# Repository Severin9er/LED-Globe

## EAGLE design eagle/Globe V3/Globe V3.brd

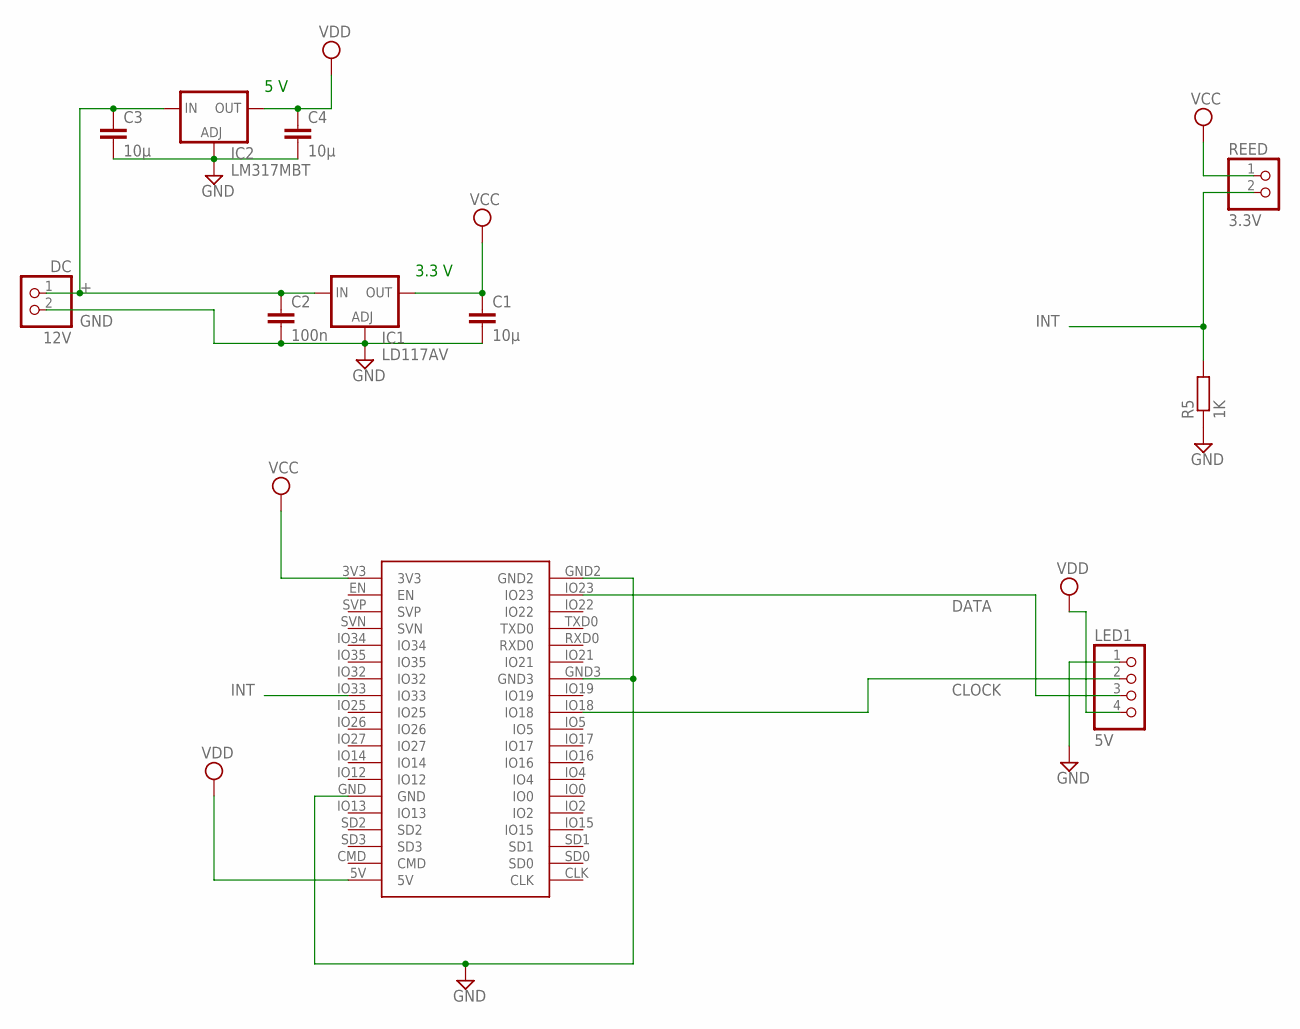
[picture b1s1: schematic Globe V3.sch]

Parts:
C1, C3, C4: 10µ; C025-024X044
C2: 100n; C050-024X044
DC: 12V; 1X02
IC1: LD117AV; TO220L1
IC2: LM317MBT; TO220L1
LED1: 5V; 1X04
R5: 1K; 0207/10
REED: 3.3V; 1X02
U$1: ESP32_DEVKITC

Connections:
+: C2.1, C3.1, DC.1, IC1.3 (IN), IC2.3 (IN)
CLOCK: LED1.2, U$1.IO18
DATA: LED1.3, U$1.IO23
GND: C1.2, C2.2, C3.2, C4.2, DC.2, IC1.1 (ADJ), IC2.1 (ADJ), LED1.1, R5.1, U$1.GND, U$1.GND2, U$1.GND3
INT: R5.2, REED.2, U$1.IO33
VCC: C1.1, IC1.2 (OUT), REED.1, U$1.3V3
VDD: C4.1, IC2.2 (OUT), LED1.4, U$1.5V

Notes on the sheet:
3.3 V
5 V

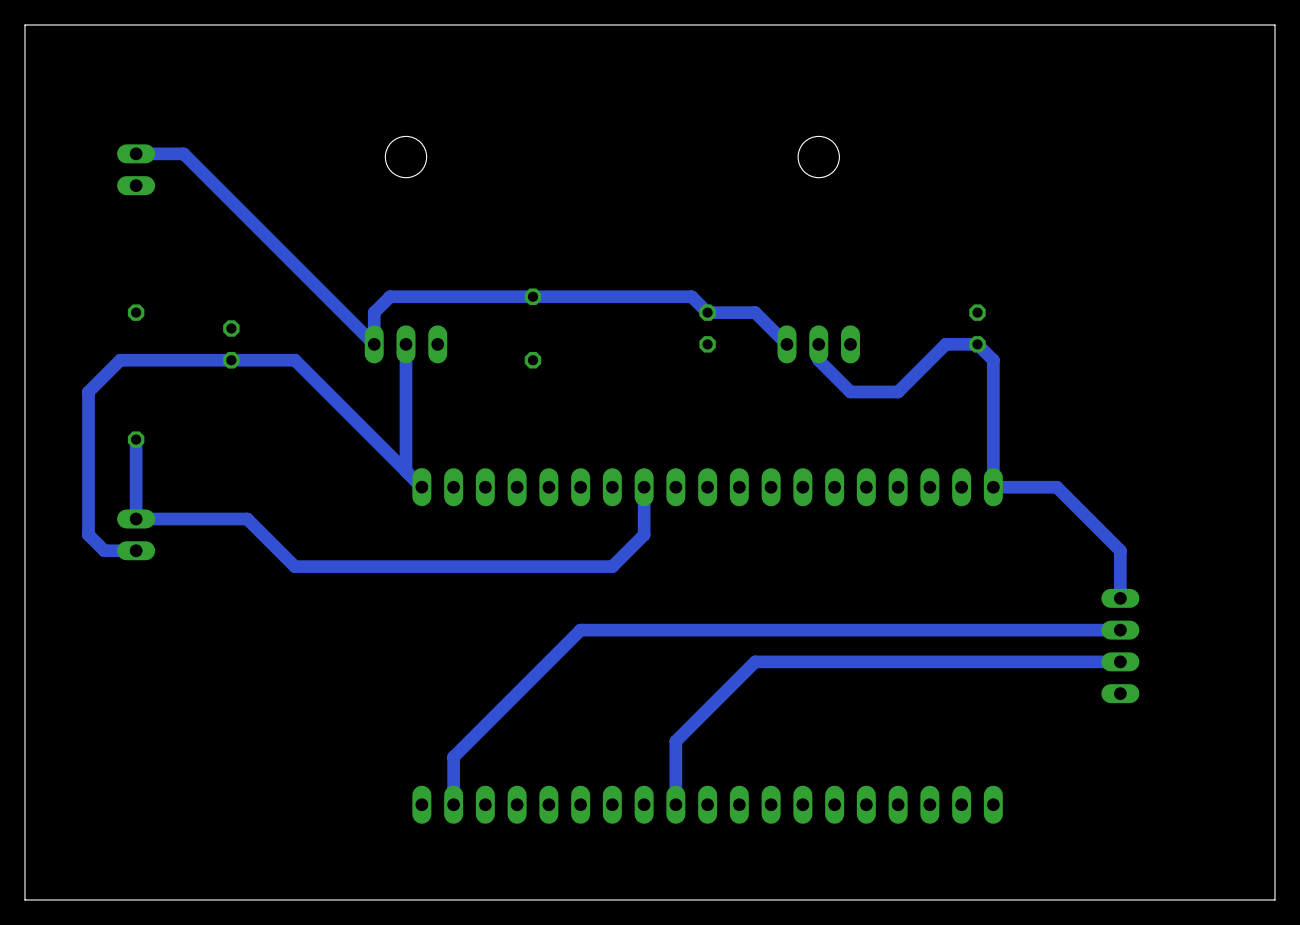
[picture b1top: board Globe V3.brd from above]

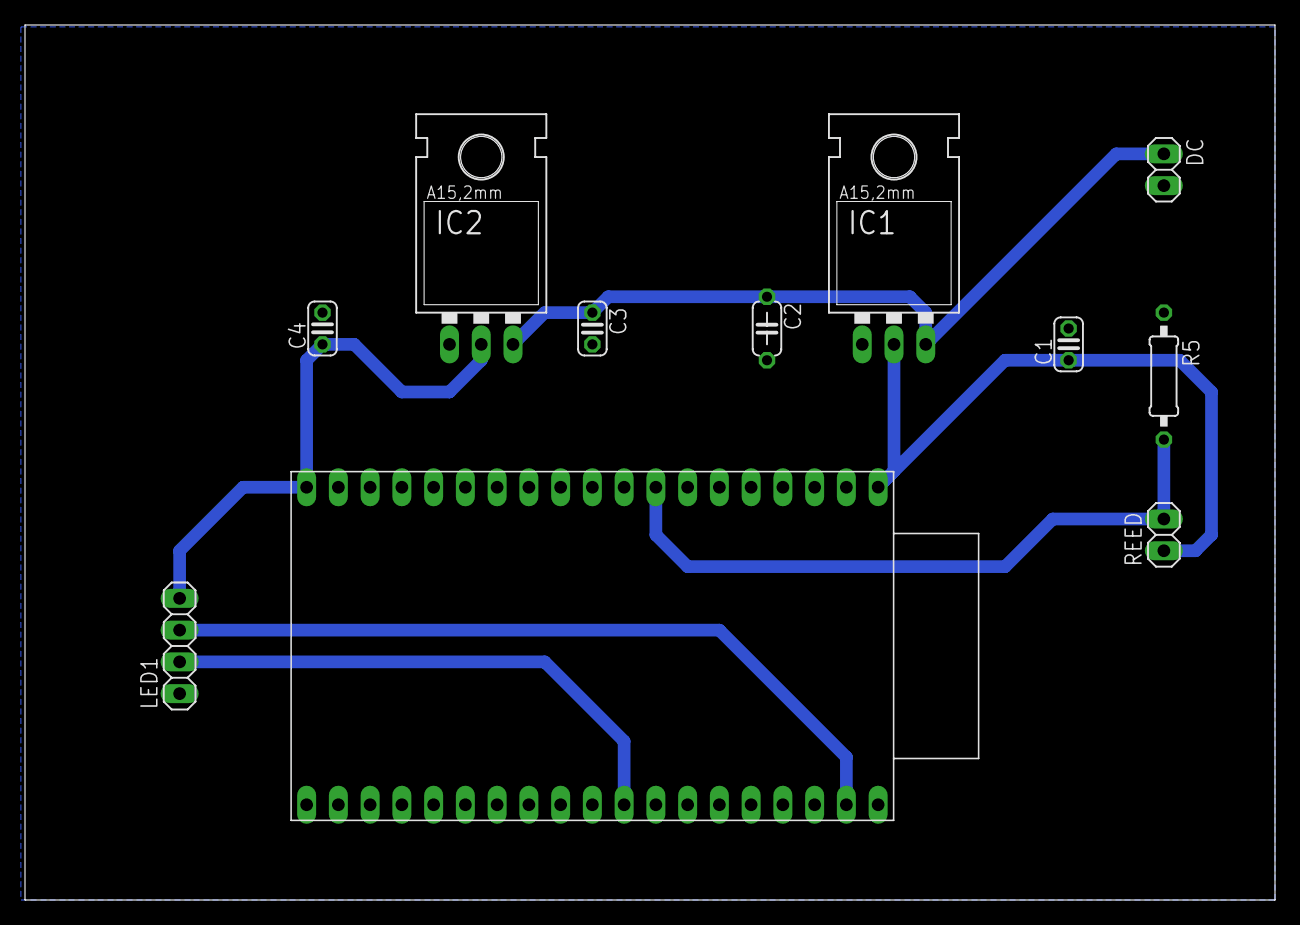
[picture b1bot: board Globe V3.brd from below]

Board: 2 copper layers, 100.0 x 70.0 mm, 11 parts (11 on the bottom side), 7 nets.

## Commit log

2018-04-20 initial commit: Data, PCBs and Software for LED-Globe
2018-04-20 remove
2018-04-20 Added again
